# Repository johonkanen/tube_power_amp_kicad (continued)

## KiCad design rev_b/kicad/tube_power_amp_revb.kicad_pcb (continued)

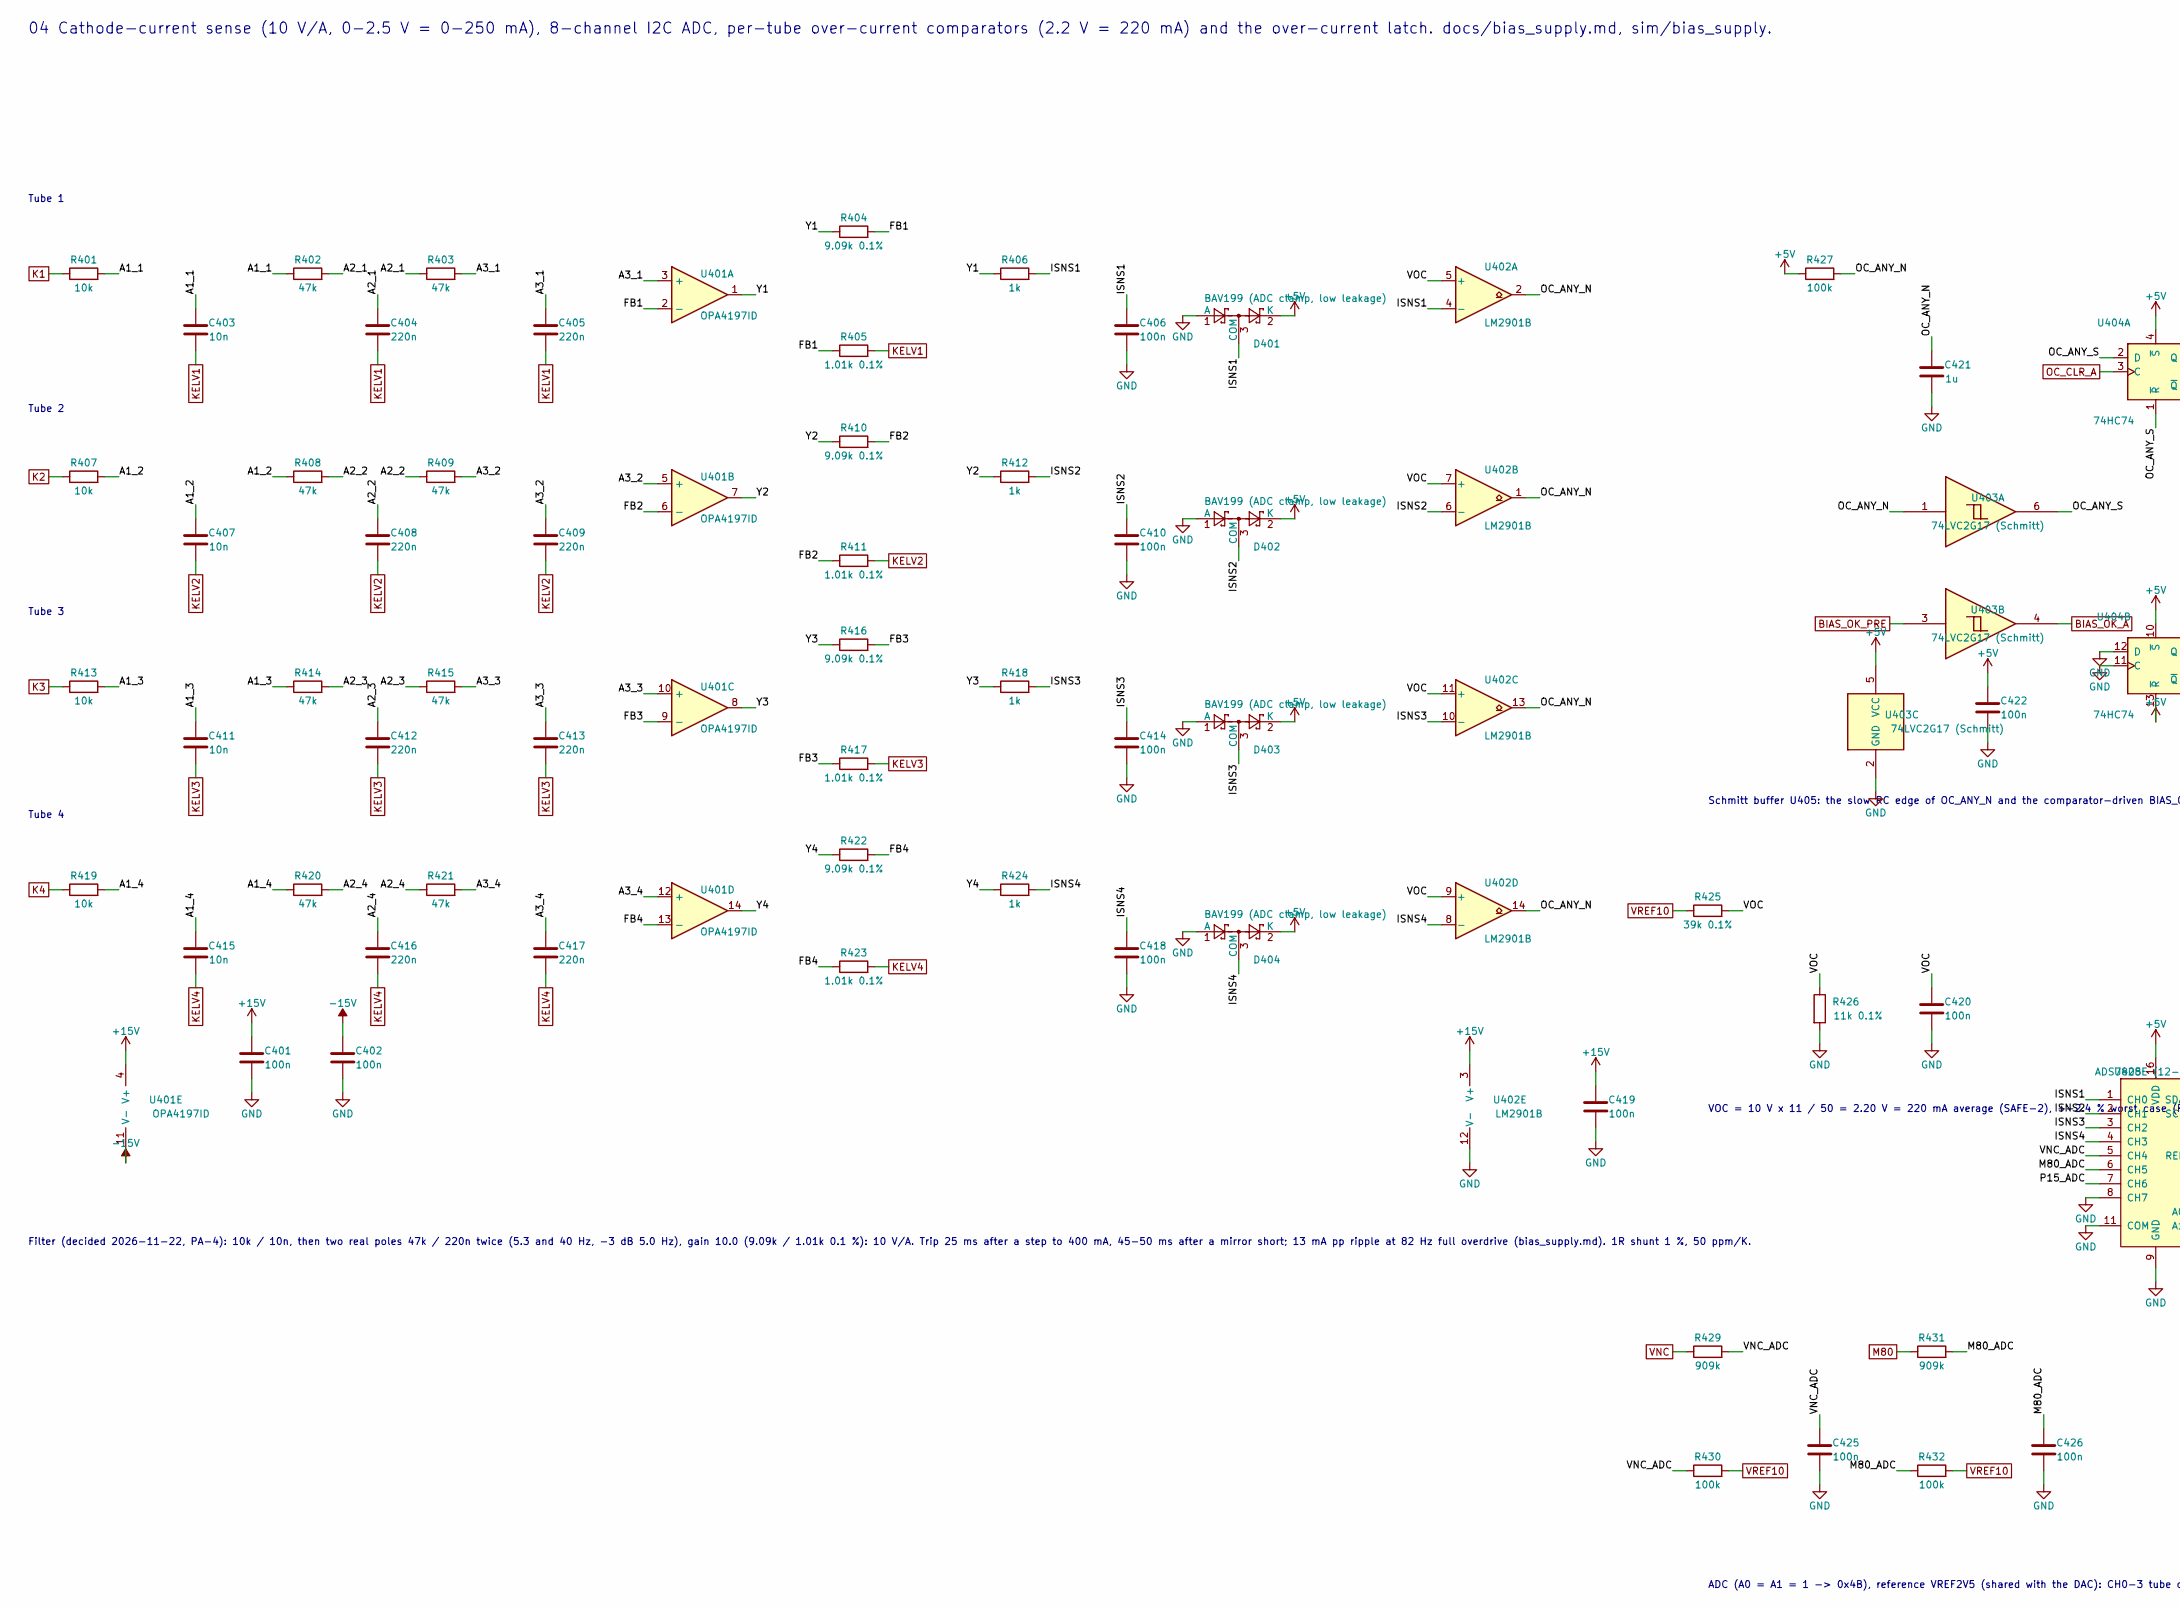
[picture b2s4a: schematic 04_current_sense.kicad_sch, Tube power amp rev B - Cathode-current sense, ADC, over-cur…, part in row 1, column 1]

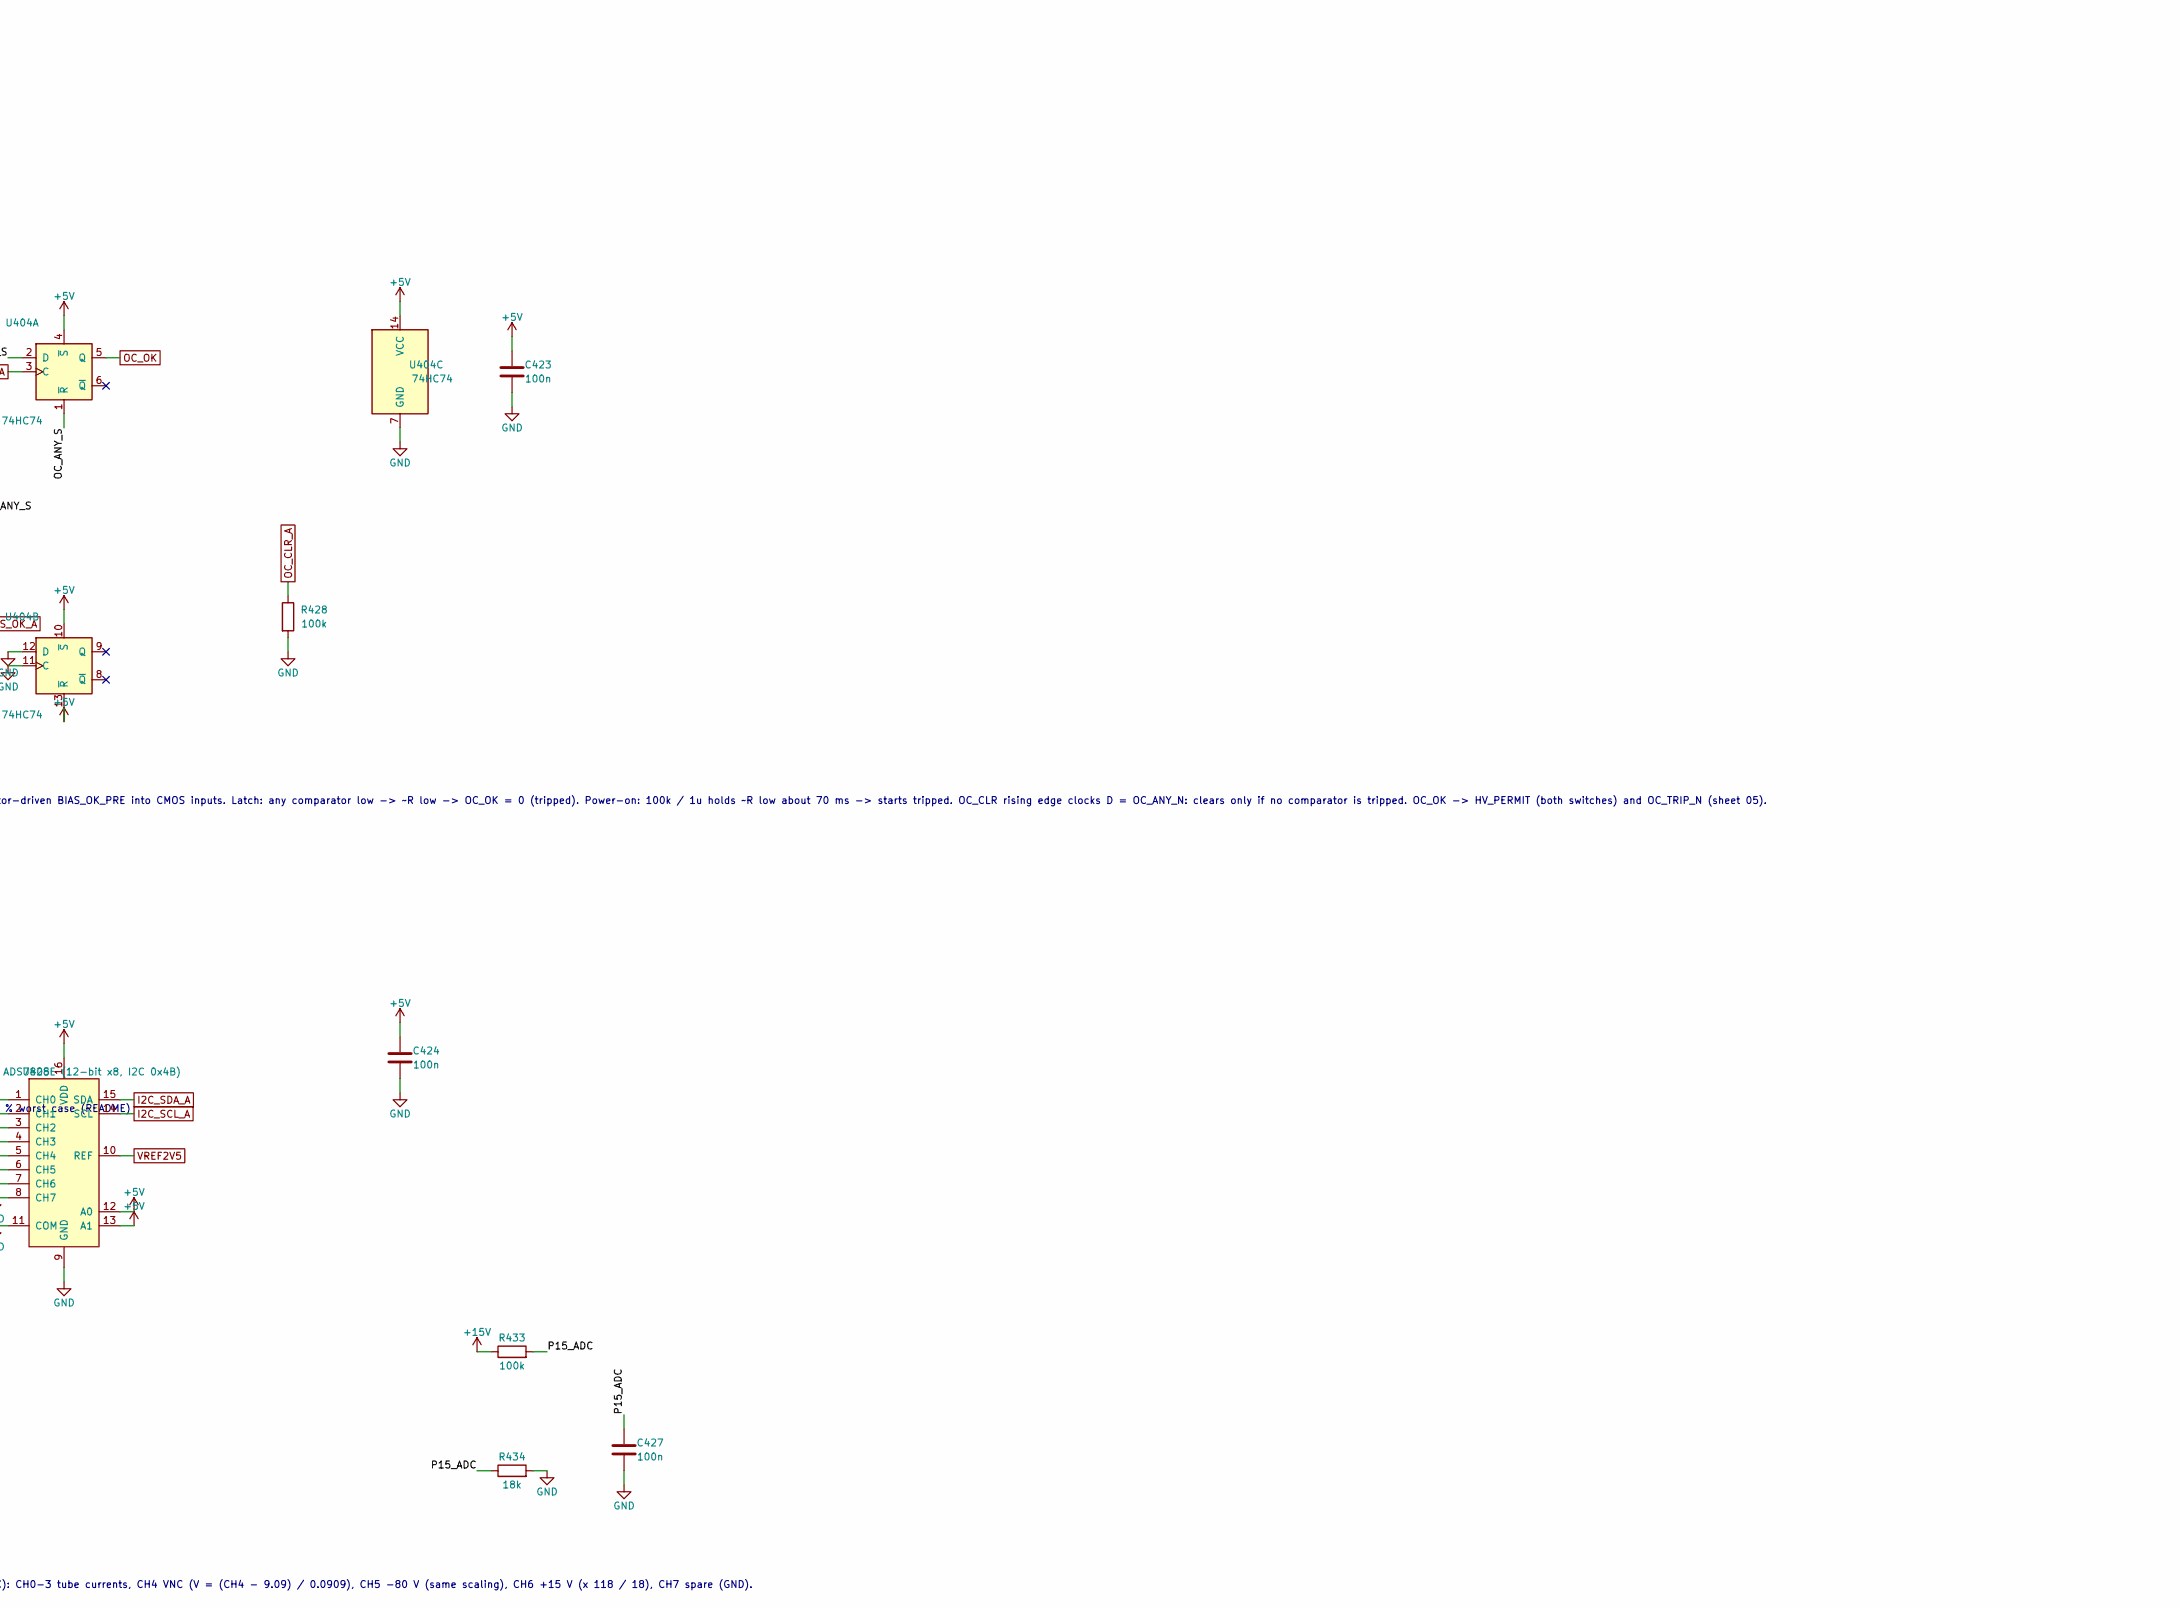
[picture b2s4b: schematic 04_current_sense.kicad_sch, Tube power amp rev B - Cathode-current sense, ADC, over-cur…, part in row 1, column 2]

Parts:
C401, C402, C406, C410, C414, C418, C419, C420, C422, C423, C424, C425, C426, C427: 100n; C_0603_1608Metric
C403, C407, C411, C415: 10n; C_0603_1608Metric
C404, C405, C408, C409, C412, C413, C416, C417: 220n; C_0805_2012Metric
C421: 1u; C_0603_1608Metric
D401, D402, D403, D404: BAV199 (ADC clamp, low leakage); SOT-23
R401, R407, R413, R419: 10k; R_0603_1608Metric
R402, R403, R408, R409, R414, R415, R420, R421: 47k; R_0603_1608Metric
R404, R410, R416, R422: 9.09k 0.1%; R_1206_3216Metric
R405, R411, R417, R423: 1.01k 0.1%; R_1206_3216Metric
R406, R412, R418, R424: 1k; R_0603_1608Metric
R425: 39k 0.1%; R_1206_3216Metric
R426: 11k 0.1%; R_1206_3216Metric
R427, R428, R430, R432, R433: 100k; R_0603_1608Metric
R429, R431: 909k; R_0603_1608Metric
R434: 18k; R_0603_1608Metric
U401: OPA4197ID; SOIC-14_3.9x8.7mm_P1.27mm
U402: LM2901B; SOIC-14_3.9x8.7mm_P1.27mm
U403: 74LVC2G17 (Schmitt); SOT-363_SC-70-6
U404: 74HC74; TSSOP-14_4.4x5mm_P0.65mm
U405: ADS7828E (12-bit x8, I2C 0x4B); TSSOP-16_4.4x5mm_P0.65mm

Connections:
+5V: C422.1, C423.1, C424.1, D401.2 (K), D402.2 (K), D403.2 (K), D404.2 (K), R427.1, U403.5 (VCC), U404.4 (~S), U404.10 (~S), U404.13 (~R), U404.14 (VCC), U405.12 (A0), U405.13 (A1), U405.16 (VDD); also elsewhere on the board
+15V: C401.1, C419.1, R433.1, U401.4 (V+), U402.3 (V+); also elsewhere on the board
-15V: C402.1, U401.11 (V-); also elsewhere on the board
/04 Cathode-current sense, ADC, over-current latch/A1_1: C403.1, R401.2, R402.1
/04 Cathode-current sense, ADC, over-current latch/A1_2: C407.1, R407.2, R408.1
/04 Cathode-current sense, ADC, over-current latch/A1_3: C411.1, R413.2, R414.1
/04 Cathode-current sense, ADC, over-current latch/A1_4: C415.1, R419.2, R420.1
/04 Cathode-current sense, ADC, over-current latch/A2_1: C404.1, R402.2, R403.1
/04 Cathode-current sense, ADC, over-current latch/A2_2: C408.1, R408.2, R409.1
/04 Cathode-current sense, ADC, over-current latch/A2_3: C412.1, R414.2, R415.1
/04 Cathode-current sense, ADC, over-current latch/A2_4: C416.1, R420.2, R421.1
/04 Cathode-current sense, ADC, over-current latch/A3_1: C405.1, R403.2, U401.3 (+)
/04 Cathode-current sense, ADC, over-current latch/A3_2: C409.1, R409.2, U401.5 (+)
/04 Cathode-current sense, ADC, over-current latch/A3_3: C413.1, R415.2, U401.10 (+)
/04 Cathode-current sense, ADC, over-current latch/A3_4: C417.1, R421.2, U401.12 (+)
/04 Cathode-current sense, ADC, over-current latch/FB1: R404.2, R405.1, U401.2 (-)
/04 Cathode-current sense, ADC, over-current latch/FB2: R410.2, R411.1, U401.6 (-)
/04 Cathode-current sense, ADC, over-current latch/FB3: R416.2, R417.1, U401.9 (-)
/04 Cathode-current sense, ADC, over-current latch/FB4: R422.2, R423.1, U401.13 (-)
/04 Cathode-current sense, ADC, over-current latch/ISNS1: C406.1, D401.3 (COM), R406.2, U402.4 (-), U405.1 (CH0)
/04 Cathode-current sense, ADC, over-current latch/ISNS2: C410.1, D402.3 (COM), R412.2, U402.6 (-), U405.2 (CH1)
/04 Cathode-current sense, ADC, over-current latch/ISNS3: C414.1, D403.3 (COM), R418.2, U402.10 (-), U405.3 (CH2)
/04 Cathode-current sense, ADC, over-current latch/ISNS4: C418.1, D404.3 (COM), R424.2, U402.8 (-), U405.4 (CH3)
/04 Cathode-current sense, ADC, over-current latch/M80_ADC: C426.1, R431.2, R432.1, U405.6 (CH5)
/04 Cathode-current sense, ADC, over-current latch/OC_ANY_N: C421.1, R427.2, U402.1, U402.2, U402.13, U402.14, U403.1
/04 Cathode-current sense, ADC, over-current latch/OC_ANY_S: U403.6, U404.1 (~R), U404.2 (D)
/04 Cathode-current sense, ADC, over-current latch/P15_ADC: C427.1, R433.2, R434.1, U405.7 (CH6)
/04 Cathode-current sense, ADC, over-current latch/VNC_ADC: C425.1, R429.2, R430.1, U405.5 (CH4)
/04 Cathode-current sense, ADC, over-current latch/VOC: C420.1, R425.2, R426.1, U402.5 (+), U402.7 (+), U402.9 (+), U402.11 (+)
/04 Cathode-current sense, ADC, over-current latch/Y1: R404.1, R406.1, U401.1
/04 Cathode-current sense, ADC, over-current latch/Y2: R410.1, R412.1, U401.7
/04 Cathode-current sense, ADC, over-current latch/Y3: R416.1, R418.1, U401.8
/04 Cathode-current sense, ADC, over-current latch/Y4: R422.1, R424.1, U401.14
BIAS_OK_A: U403.4; also elsewhere on the board
BIAS_OK_PRE: U403.3; also elsewhere on the board
GND: C401.2, C402.2, C406.2, C410.2, C414.2, C418.2, C419.2, C420.2, C421.2, C422.2, C423.2, C424.2, C425.2, C426.2, C427.2, D401.1 (A), D402.1 (A), D403.1 (A), D404.1 (A), R426.2, R428.2, R434.2, U402.12 (V-), U403.2 (GND), U404.7 (GND), U404.11 (C), U404.12 (D), U405.8 (CH7), U405.9 (GND), U405.11 (COM); also elsewhere on the board
I2C_SCL_A: U405.14 (SCL); also elsewhere on the board
I2C_SDA_A: U405.15 (SDA); also elsewhere on the board
K1: R401.1; also elsewhere on the board
K2: R407.1; also elsewhere on the board
K3: R413.1; also elsewhere on the board
K4: R419.1; also elsewhere on the board
KELV1: C403.2, C404.2, C405.2, R405.2; also elsewhere on the board
KELV2: C407.2, C408.2, C409.2, R411.2; also elsewhere on the board
KELV3: C411.2, C412.2, C413.2, R417.2; also elsewhere on the board
KELV4: C415.2, C416.2, C417.2, R423.2; also elsewhere on the board
M80: R431.1; also elsewhere on the board
OC_CLR_A: R428.1, U404.3 (C); also elsewhere on the board
OC_OK: U404.5 (Q); also elsewhere on the board
VNC: R429.1; also elsewhere on the board
VREF2V5: U405.10 (REF); also elsewhere on the board
VREF10: R425.1, R430.2, R432.2; also elsewhere on the board

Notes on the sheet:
04 Cathode-current sense (10 V/A, 0-2.5 V = 0-250 mA), 8-channel I2C ADC, per-tube over-current comparators (2.2 V = 220 mA) and the over-current latch. docs/bias_supply.md, sim/bias_supply.
Tube 1
Tube 2
Tube 3
Tube 4
Filter (decided 2026-11-22, PA-4): 10k / 10n, then two real poles 47k / 220n twice (5.3 and 40 Hz, -3 dB 5.0 Hz), gain 10.0 (9.09k / 1.01k 0.1 %): 10 V/A. Trip 25 ms after a step to 400 mA, 45-50 ms after a mirror short; 13 mA pp ripple at 82 Hz full overdrive (bias_supply.md). 1R shunt 1 %, 50 ppm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
VOC = 10 V x 11 / 50 = 2.20 V = 220 mA average (SAFE-2), +-2.4 % worst case (README)
Schmitt buffer U405: the slow RC edge of OC_ANY_N and the comparator-driven BIAS_OK_PRE into CMOS inputs. Latch: any comparator low -> ~R low -> OC_OK = 0 (tripped). Power-on: 100k / 1u holds ~R low about 70 ms -> starts tripped. OC_CLR rising edge clocks D = OC_ANY_N: clears only if no comparator 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
ADC (A0 = A1 = 1 -> 0x4B), reference VREF2V5 (shared with the DAC): CH0-3 tube currents, CH4 VNC (V = (CH4 - 9.09) / 0.0909), CH5 -80 V (same scaling), CH6 +15 V (x 118 / 18), CH7 spare (GND).

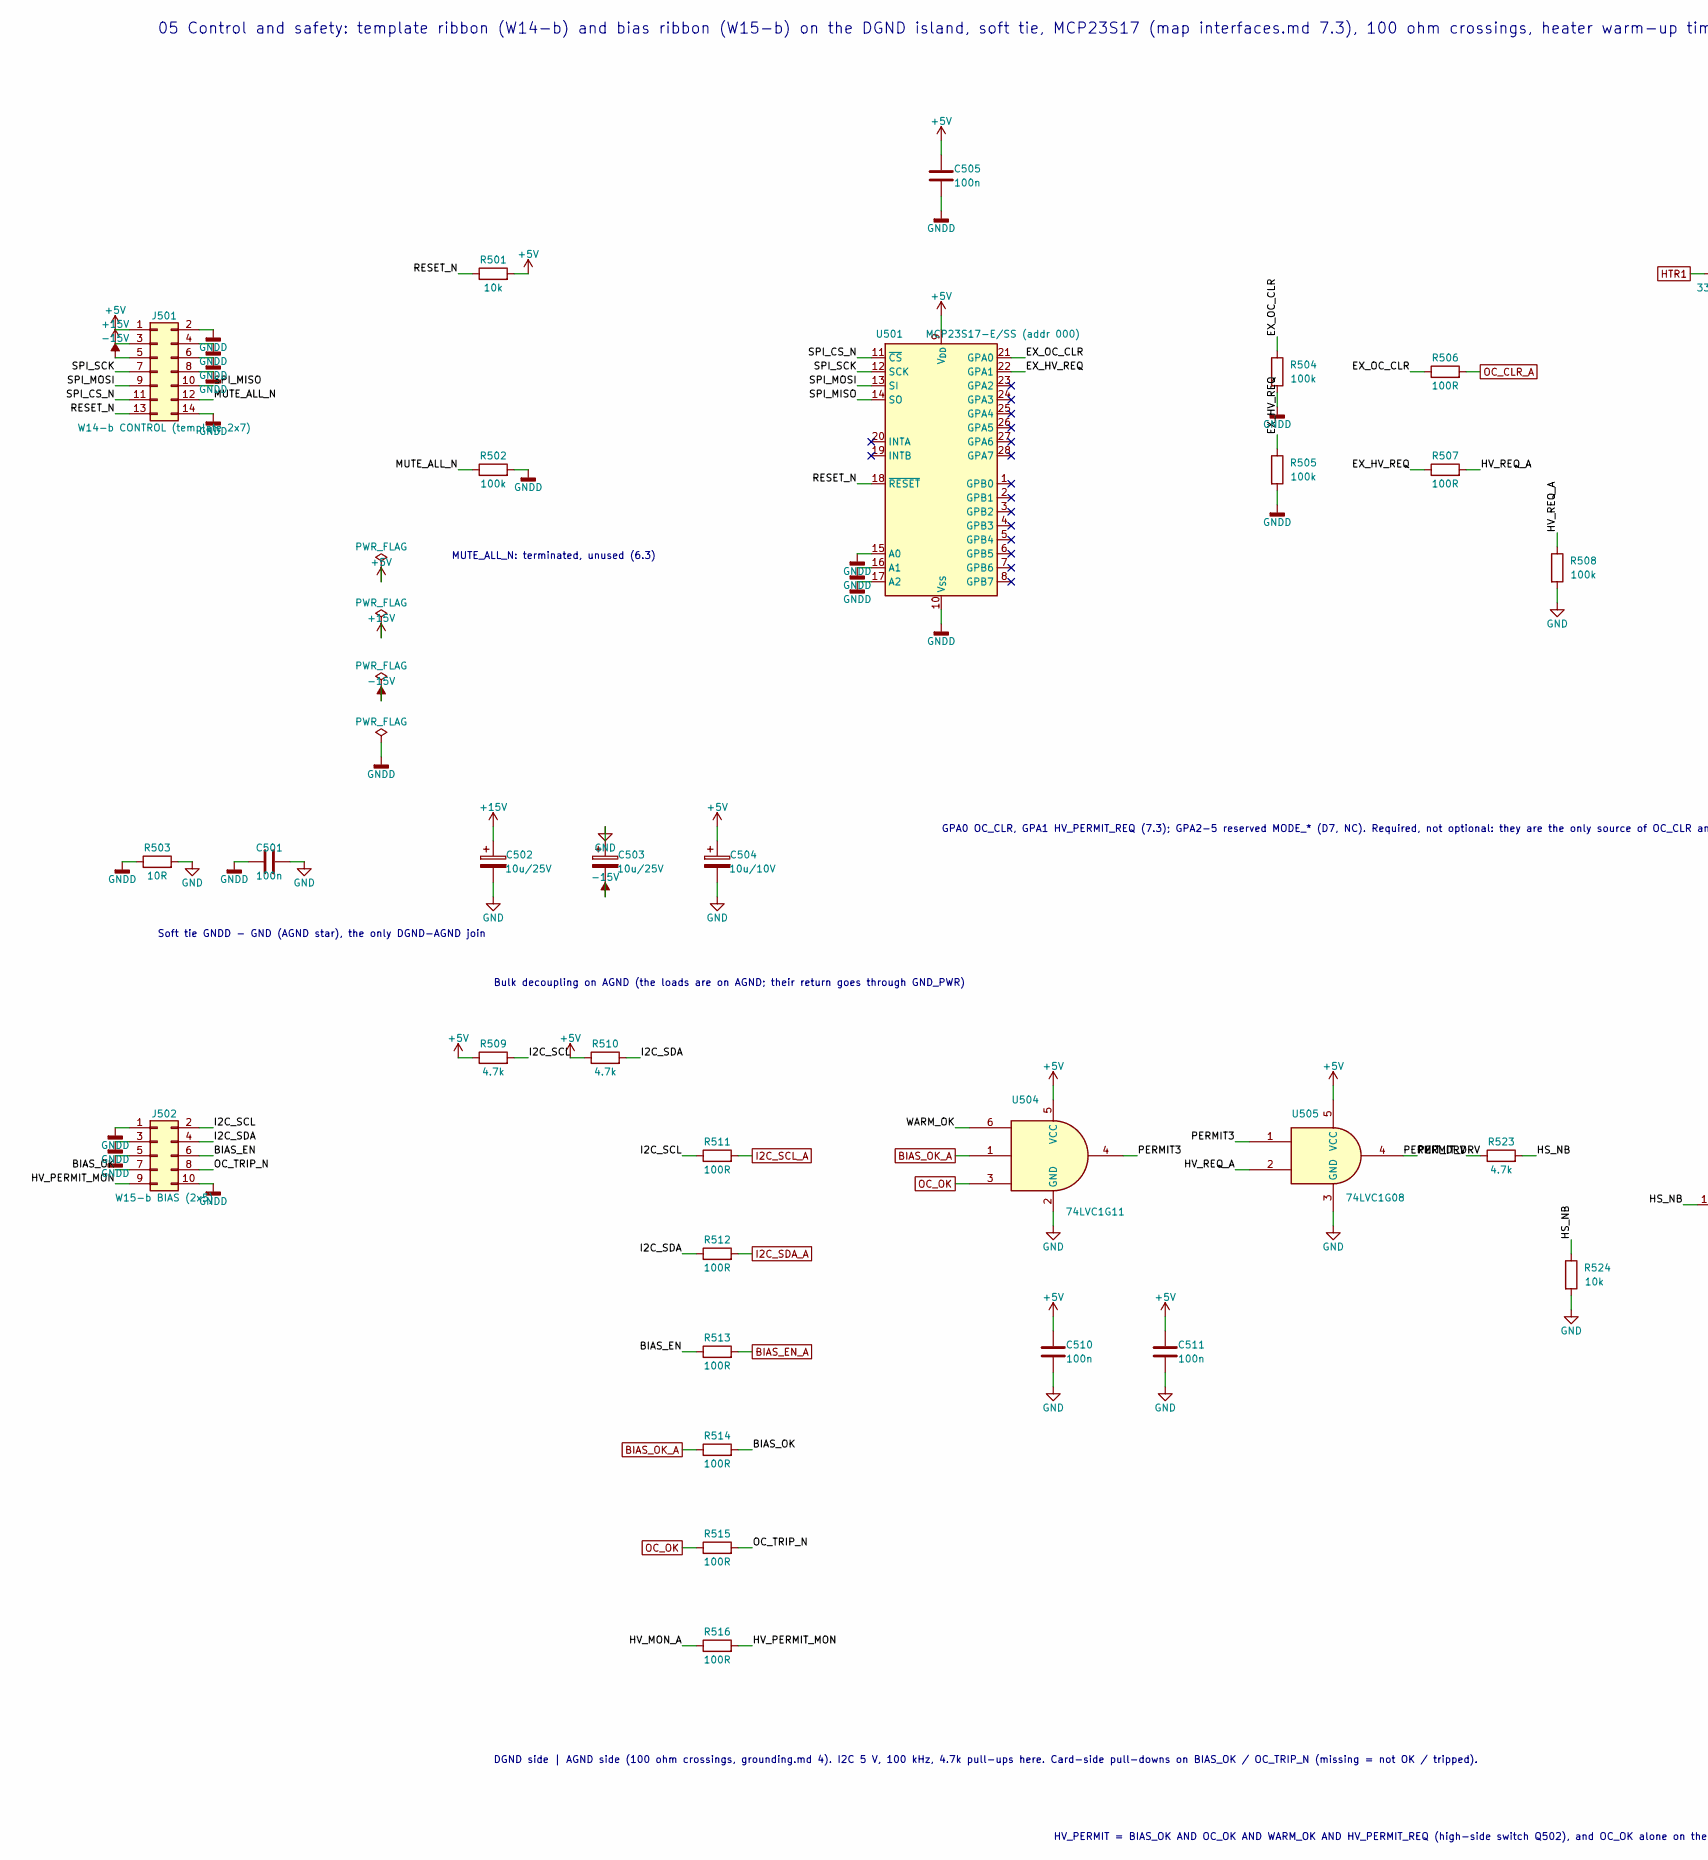
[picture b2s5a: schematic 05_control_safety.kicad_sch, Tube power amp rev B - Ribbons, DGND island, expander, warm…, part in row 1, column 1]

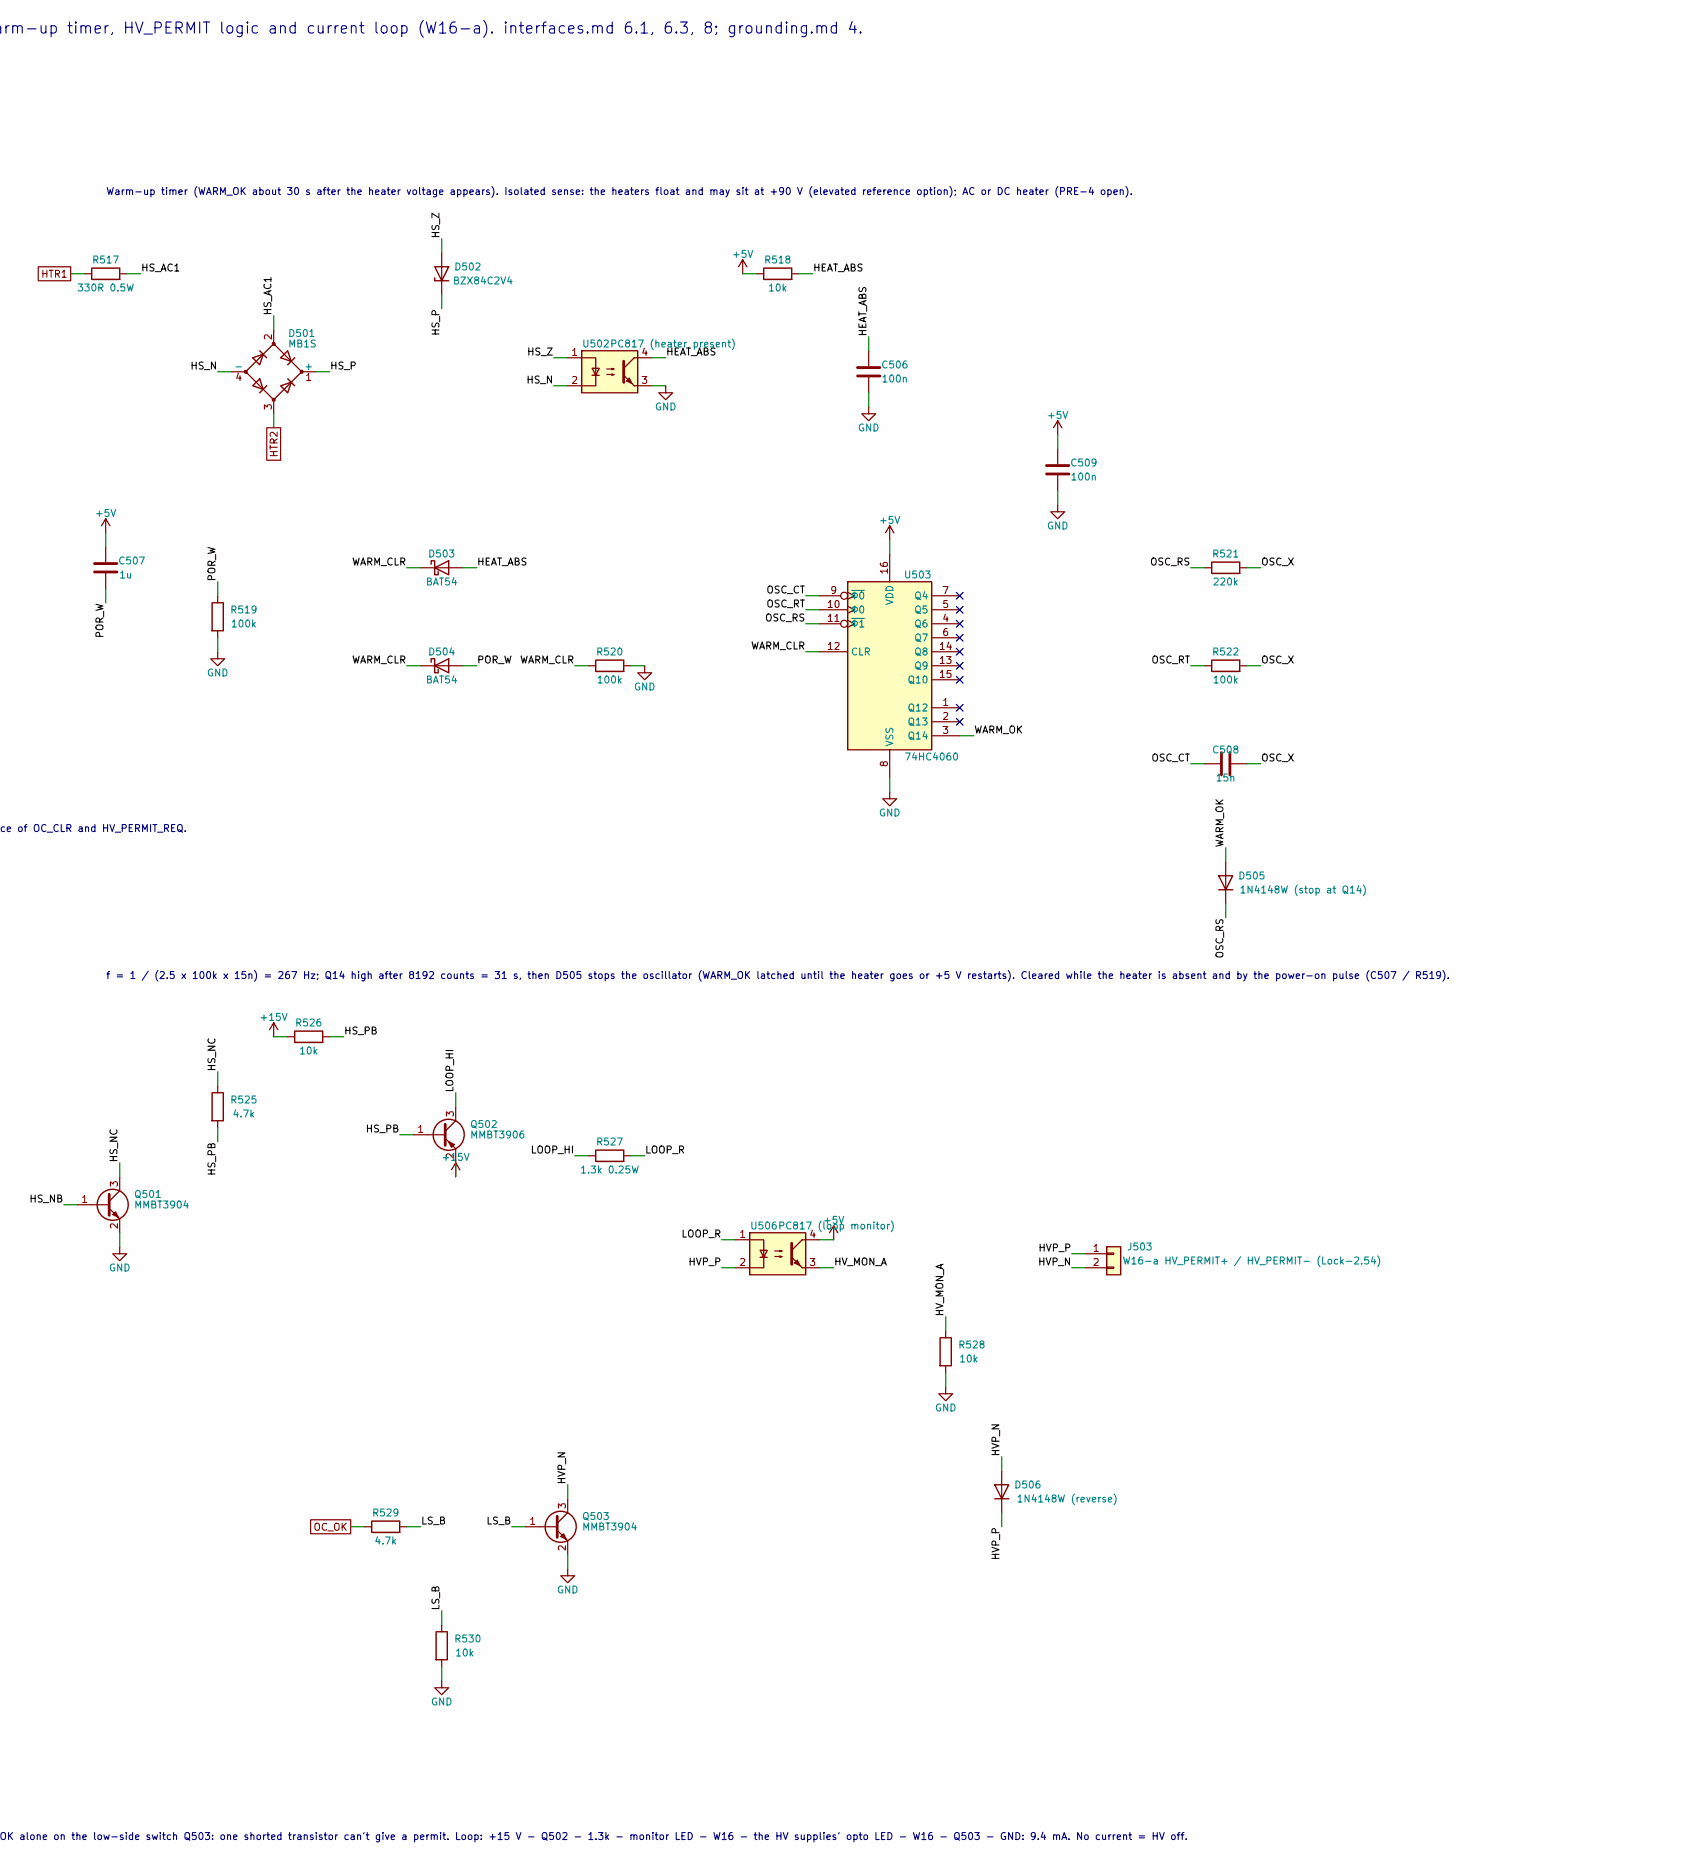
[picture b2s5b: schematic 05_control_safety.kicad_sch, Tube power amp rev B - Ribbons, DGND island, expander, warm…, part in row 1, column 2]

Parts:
C501, C505, C506, C509, C510, C511: 100n; C_0603_1608Metric
C502, C503: 10u/25V; C_1206_3216Metric
C504: 10u/10V; C_1206_3216Metric
C507: 1u; C_0603_1608Metric
C508: 15n; C_0603_1608Metric
D501: MB1S; TO-269AA
D502: BZX84C2V4; SOT-23
D503, D504: BAT54; D_SOD-323
D505: 1N4148W (stop at Q14); D_SOD-123
D506: 1N4148W (reverse); D_SOD-123
J501: W14-b CONTROL (template 2x7); IDC-Header_2x07_P2.54mm_Vertical
J502: W15-b BIAS (2x5); IDC-Header_2x05_P2.54mm_Vertical
J503: W16-a HV_PERMIT+ / HV_PERMIT- (Lock-2.54); Molex_KK-254_AE-6410-02A_1x02_P2.54mm_Vertical
Q501, Q503: MMBT3904; SOT-23
Q502: MMBT3906; SOT-23
R501, R518, R524, R526, R528, R530: 10k; R_0603_1608Metric
R502, R504, R505, R508, R519, R520, R522: 100k; R_0603_1608Metric
R503: 10R; R_0603_1608Metric
R506, R507, R511, R512, R513, R514, R515, R516: 100R; R_0603_1608Metric
R509, R510, R523, R525, R529: 4.7k; R_0603_1608Metric
R517: 330R 0.5W; R_1206_3216Metric
R521: 220k; R_0603_1608Metric
R527: 1.3k 0.25W; R_1206_3216Metric
U501: MCP23S17-E/SS (addr 000); SSOP-28_5.3x10.2mm_P0.65mm
U502: PC817 (heater present); SMDIP-4_W7.62mm
U503: 74HC4060; SOIC-16_3.9x9.9mm_P1.27mm
U504: 74LVC1G11; SOT-363_SC-70-6
U505: 74LVC1G08; SOT-353_SC-70-5
U506: PC817 (loop monitor); SMDIP-4_W7.62mm

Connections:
+5V: C504.1, C505.1, C507.1, C509.1, C510.1, C511.1, J501.1, R501.2, R509.1, R510.1, R518.1, U501.9 (V_{DD}), U503.16 (VDD), U504.5 (VCC), U505.5 (VCC), U506.4; also elsewhere on the board
+15V: C502.1, J501.3, Q502.2 (E), R526.1; also elsewhere on the board
-15V: C503.2, J501.5; also elsewhere on the board
/05 Ribbons, DGND island, expander, warm-up timer, HV_PERMIT/BIAS_EN: J502.6, R513.1
/05 Ribbons, DGND island, expander, warm-up timer, HV_PERMIT/BIAS_OK: J502.7, R514.2
/05 Ribbons, DGND island, expander, warm-up timer, HV_PERMIT/EX_HV_REQ: R505.1, R507.1, U501.22 (GPA1)
/05 Ribbons, DGND island, expander, warm-up timer, HV_PERMIT/EX_OC_CLR: R504.1, R506.1, U501.21 (GPA0)
/05 Ribbons, DGND island, expander, warm-up timer, HV_PERMIT/HEAT_ABS: C506.1, D503.2 (A), R518.2, U502.4
/05 Ribbons, DGND island, expander, warm-up timer, HV_PERMIT/HS_AC1: D501.2, R517.2
/05 Ribbons, DGND island, expander, warm-up timer, HV_PERMIT/HS_N: D501.4 (-), U502.2
/05 Ribbons, DGND island, expander, warm-up timer, HV_PERMIT/HS_NB: Q501.1 (B), R523.2, R524.1
/05 Ribbons, DGND island, expander, warm-up timer, HV_PERMIT/HS_NC: Q501.3 (C), R525.1
/05 Ribbons, DGND island, expander, warm-up timer, HV_PERMIT/HS_P: D501.1 (+), D502.1 (K)
/05 Ribbons, DGND island, expander, warm-up timer, HV_PERMIT/HS_PB: Q502.1 (B), R525.2, R526.2
/05 Ribbons, DGND island, expander, warm-up timer, HV_PERMIT/HS_Z: D502.2 (A), U502.1
/05 Ribbons, DGND island, expander, warm-up timer, HV_PERMIT/HVP_N: D506.2 (A), J503.2, Q503.3 (C)
/05 Ribbons, DGND island, expander, warm-up timer, HV_PERMIT/HVP_P: D506.1 (K), J503.1, U506.2
/05 Ribbons, DGND island, expander, warm-up timer, HV_PERMIT/HV_MON_A: R516.1, R528.1, U506.3
/05 Ribbons, DGND island, expander, warm-up timer, HV_PERMIT/HV_PERMIT_MON: J502.9, R516.2
/05 Ribbons, DGND island, expander, warm-up timer, HV_PERMIT/HV_REQ_A: R507.2, R508.1, U505.2
/05 Ribbons, DGND island, expander, warm-up timer, HV_PERMIT/I2C_SCL: J502.2, R509.2, R511.1
/05 Ribbons, DGND island, expander, warm-up timer, HV_PERMIT/I2C_SDA: J502.4, R510.2, R512.1
/05 Ribbons, DGND island, expander, warm-up timer, HV_PERMIT/LOOP_HI: Q502.3 (C), R527.1
/05 Ribbons, DGND island, expander, warm-up timer, HV_PERMIT/LOOP_R: R527.2, U506.1
/05 Ribbons, DGND island, expander, warm-up timer, HV_PERMIT/LS_B: Q503.1 (B), R529.2, R530.1
/05 Ribbons, DGND island, expander, warm-up timer, HV_PERMIT/MUTE_ALL_N: J501.12, R502.1
/05 Ribbons, DGND island, expander, warm-up timer, HV_PERMIT/OC_TRIP_N: J502.8, R515.2
/05 Ribbons, DGND island, expander, warm-up timer, HV_PERMIT/OSC_CT: C508.1, U503.9 (~Φ0)
/05 Ribbons, DGND island, expander, warm-up timer, HV_PERMIT/OSC_RS: D505.1 (K), R521.1, U503.11 (~Φ1)
/05 Ribbons, DGND island, expander, warm-up timer, HV_PERMIT/OSC_RT: R522.1, U503.10 (Φ0)
/05 Ribbons, DGND island, expander, warm-up timer, HV_PERMIT/OSC_X: C508.2, R521.2, R522.2
/05 Ribbons, DGND island, expander, warm-up timer, HV_PERMIT/PERMIT3: U504.4, U505.1
/05 Ribbons, DGND island, expander, warm-up timer, HV_PERMIT/PERMIT_DRV: R523.1, U505.4
/05 Ribbons, DGND island, expander, warm-up timer, HV_PERMIT/POR_W: C507.2, D504.2 (A), R519.1
/05 Ribbons, DGND island, expander, warm-up timer, HV_PERMIT/RESET_N: J501.13, R501.1, U501.18 (~RESET)
/05 Ribbons, DGND island, expander, warm-up timer, HV_PERMIT/SPI_CS_N: J501.11, U501.11 (~CS)
/05 Ribbons, DGND island, expander, warm-up timer, HV_PERMIT/SPI_MISO: J501.10, U501.14 (SO)
/05 Ribbons, DGND island, expander, warm-up timer, HV_PERMIT/SPI_MOSI: J501.9, U501.13 (SI)
/05 Ribbons, DGND island, expander, warm-up timer, HV_PERMIT/SPI_SCK: J501.7, U501.12 (SCK)
/05 Ribbons, DGND island, expander, warm-up timer, HV_PERMIT/WARM_CLR: D503.1 (K), D504.1 (K), R520.1, U503.12 (CLR)
/05 Ribbons, DGND island, expander, warm-up timer, HV_PERMIT/WARM_OK: D505.2 (A), U503.3 (Q14), U504.6
BIAS_EN_A: R513.2; also elsewhere on the board
BIAS_OK_A: R514.1, U504.1; also elsewhere on the board
GND: C501.2, C502.2, C503.1, C504.2, C506.2, C509.2, C510.2, C511.2, Q501.2 (E), Q503.2 (E), R503.2, R508.2, R519.2, R520.2, R524.2, R528.2, R530.2, U502.3, U503.8 (VSS), U504.2 (GND), U505.3 (GND); also elsewhere on the board
GNDD: C501.1, C505.2, J501.2, J501.4, J501.6, J501.8, J501.14, J502.1, J502.3, J502.5, J502.10, R502.2, R503.1, R504.2, R505.2, U501.10 (V_{SS}), U501.15 (A0), U501.16 (A1), U501.17 (A2); also elsewhere on the board
HTR1: R517.1; also elsewhere on the board
HTR2: D501.3; also elsewhere on the board
I2C_SCL_A: R511.2; also elsewhere on the board
I2C_SDA_A: R512.2; also elsewhere on the board
OC_CLR_A: R506.2; also elsewhere on the board
OC_OK: R515.1, R529.1, U504.3; also elsewhere on the board

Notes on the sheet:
05 Control and safety: template ribbon (W14-b) and bias ribbon (W15-b) on the DGND island, soft tie, MCP23S17 (map interfaces.md 7.3), 100 ohm crossings, heater warm-up timer, HV_PERMIT logic and current loop (W16-a). interfaces.md 6.1, 6.3, 8; grounding.md 4.
MUTE_ALL_N: terminated, unused (6.3)
Soft tie GNDD - GND (AGND star), the only DGND-AGND join
Bulk decoupling on AGND (the loads are on AGND; their return goes through GND_PWR)
GPA0 OC_CLR, GPA1 HV_PERMIT_REQ (7.3); GPA2-5 reserved MODE_* (D7, NC). Required, not optional: they are the only source of OC_CLR and HV_PERMIT_REQ.
DGND side | AGND side (100 ohm crossings, grounding.md 4). I2C 5 V, 100 kHz, 4.7k pull-ups here. Card-side pull-downs on BIAS_OK / OC_TRIP_N (missing = not OK / tripped).
Warm-up timer (WARM_OK about 30 s after the heater voltage appears). Isolated sense: the heaters float and may sit at +90 V (elevated reference option); AC or DC heater (PRE-4 open).
f = 1 / (2.5 x 100k x 15n) = 267 Hz; Q14 high after 8192 counts = 31 s, then D505 stops the oscillator (WARM_OK latched until the heater goes or +5 V restarts). Cleared while the heater is absent and by the power-on pulse (C507 / R519).
HV_PERMIT = BIAS_OK AND OC_OK AND WARM_OK AND HV_PERMIT_REQ (high-side switch Q502), and OC_OK alone on the low-side switch Q503: one shorted transistor can't give a permit. Loop: +15 V - Q502 - 1.3k - monitor LED - W16 - the HV supplies' opto LED - W16 - Q503 - GND: 9.4 mA. No current = HV off.
